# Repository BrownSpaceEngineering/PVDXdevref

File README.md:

# PVDX device reference

Datasheets for the PVDX cubesat peripherals w/ RAG

## Add a datasheet

1. Copy the PDF into `original/<peripheral>/`.
2. Run `uv run main.py ingest`.
3. Commit the new files in `original/` and `markdown/`.

The ingest step converts only new or changed files, so a second run is fast.

## GPU Acceleration

You can go super fast crazy mode by running on GPU if you have a CUDA-compatible NVIDIA gpu.
Run `uv run --extra gpu python -u main.py ingest`.

## Search

```
uv run main.py search "WHO_AM_I register" -k 5 --part 9-axis
```

## Layout

- `original/` source files provided by humans
- `markdown/` generated Markdown
- `index/` ingest-generated search index
- `boards/` KiCad board designs (schematics, PCB, gerbers), copied from the board repos

## Note on Datasheet Availability

All datasheets are made available in `original/` to the public except for those pertaining
to the CUBECOM STX-G2/VESTALINK, which are provided to BSE by CUBECOM. If you need these,
please request them from Alex Khosrowshahi (spoonmilk) or Alicia Wu.

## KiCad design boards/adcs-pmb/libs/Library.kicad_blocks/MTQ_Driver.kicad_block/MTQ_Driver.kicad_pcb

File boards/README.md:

# PVDX board designs

KiCad projects for the PVDX boards, copied from their BrownSpaceEngineering repos (not submodules).
The upstream repos are the source of truth for ongoing design work; re-copy to update.

KiCad lock files, `-backups/`, autosaves, `fp-info-cache`, `.kicad_prl`, and `.bak` files were left out.

| Folder | Upstream repo | Commit | Contents |
| --- | --- | --- | --- |
| `battery-board/` | [PVDX-Battery-Board](https://github.com/BrownSpaceEngineering/PVDX-Battery-Board) | `92fe52d` (2026-10-13) | Battery stack, heaters, thermistors; gerbers in `manufacturing/` |
| `compute-board/` | [PVDX-Compute-Board](https://github.com/BrownSpaceEngineering/PVDX-Compute-Board) | `c12a1c8` (2026-10-01) | SAMD51 compute board (2-layer `Compute Board/`, 4-layer `compute4layer/`), dev board, shared `Components/` |
| `solar-boards/` | [SolarBoards](https://github.com/BrownSpaceEngineering/SolarBoards) | `316883e` (2026-09-24) | Solar PCBs: `SolarPCB_Arm`, `SolarPCB_Long`, `SolarPCB_Short` with gerbers |
| `uhf-balun-board/` | [uhf-balun-board](https://github.com/BrownSpaceEngineering/uhf-balun-board) | `b9d6cff` (2026-09-22) | UHF balun board (newer revision, adds plated through-holes); gerbers in `gerbers/` |
| `balun-board/` | [balun-board](https://github.com/BrownSpaceEngineering/balun-board) | `164e4f9` (2026-09-16) | Earlier revision of the UHF balun board |
| `adcs-pmb/` | [PVDX-ADCS-PMB](https://github.com/BrownSpaceEngineering/PVDX-ADCS-PMB) | `089a12e` (2026-09-29) | ADCS + perovskite measurement board: photodiode amplifiers, magnetorquer drivers, perovskite pixel switching (`schematics/`); gerbers and plots in `manufacturing/` |
| `magnetorquer-board/` | [magnetorquer-board](https://github.com/BrownSpaceEngineering/magnetorquer-board) | `9018ce9` (2025-10-23) | Magnetorquer board |

Schematics are in `*.kicad_sch` files. These are plain-text S-expressions, so you can grep them for
symbol references, net labels, and part values.

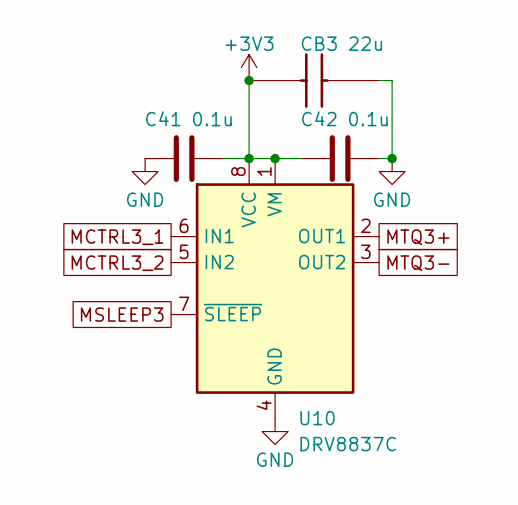
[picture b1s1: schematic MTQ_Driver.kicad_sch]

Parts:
C41, C42: 0.1u; C_0603_1608Metric
CB3: 22u; GRM18x; Mouser Part Number 81-GRM188R61A226ME5D
U10: DRV8837C; DSG8_P9X1P6_TEX

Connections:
+3V3: C41.2, C42.1, CB3.1, U10.1 (VM), U10.8 (VCC)
GND: C41.1, C42.2, CB3.2, U10.4 (GND), U10.9 (GND)
MCTRL3_1: U10.6 (IN1)
MCTRL3_2: U10.5 (IN2)
MSLEEP3: U10.7 (~SLEEP)
MTQ3+: U10.2 (OUT1)
MTQ3-: U10.3 (OUT2)

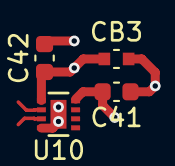
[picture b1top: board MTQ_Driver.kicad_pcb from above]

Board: 4 copper layers, 4 parts (0 on the bottom side), 2 nets.

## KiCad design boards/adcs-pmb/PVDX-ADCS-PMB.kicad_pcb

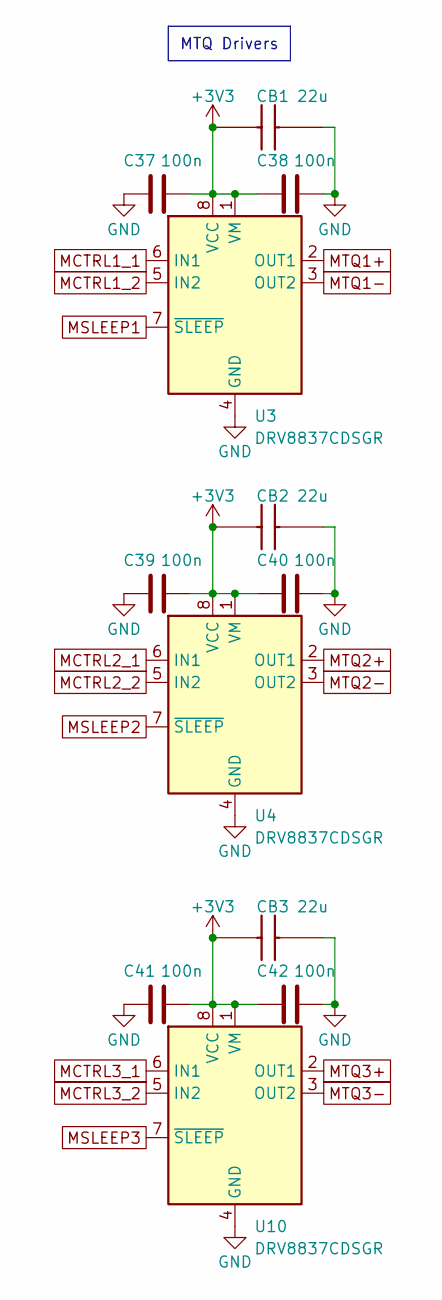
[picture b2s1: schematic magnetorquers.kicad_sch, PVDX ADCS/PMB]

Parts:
C37, C38, C39, C40, C41, C42: 100n; C_0603_1608Metric
CB1, CB2, CB3: 22u; GRM18x; Mouser Part Number 81-GRM188R61A226ME5D
U3, U4, U10: DRV8837CDSGR; DSG8_P9X1P6_TEX; Manufacturer_Part_Number DRV8837CDSGR

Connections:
+3V3: C37.2, C38.1, C39.2, C40.1, C41.2, C42.1, CB1.1, CB2.1, CB3.1, U3.1 (VM), U3.8 (VCC), U4.1 (VM), U4.8 (VCC), U10.1 (VM), U10.8 (VCC); also elsewhere on the board
GND: C37.1, C38.2, C39.1, C40.2, C41.1, C42.2, CB1.2, CB2.2, CB3.2, U3.4 (GND), U3.9 (GND), U4.4 (GND), U4.9 (GND), U10.4 (GND), U10.9 (GND); also elsewhere on the board
MCTRL1_1: U3.6 (IN1); also elsewhere on the board
MCTRL1_2: U3.5 (IN2); also elsewhere on the board
MCTRL2_1: U4.6 (IN1); also elsewhere on the board
MCTRL2_2: U4.5 (IN2); also elsewhere on the board
MCTRL3_1: U10.6 (IN1); also elsewhere on the board
MCTRL3_2: U10.5 (IN2); also elsewhere on the board
MSLEEP1: U3.7 (~SLEEP); also elsewhere on the board
MSLEEP2: U4.7 (~SLEEP); also elsewhere on the board
MSLEEP3: U10.7 (~SLEEP); also elsewhere on the board
MTQ1+: U3.2 (OUT1); also elsewhere on the board
MTQ1-: U3.3 (OUT2); also elsewhere on the board
MTQ2+: U4.2 (OUT1); also elsewhere on the board
MTQ2-: U4.3 (OUT2); also elsewhere on the board
MTQ3+: U10.2 (OUT1); also elsewhere on the board
MTQ3-: U10.3 (OUT2); also elsewhere on the board

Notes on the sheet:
MTQ Drivers

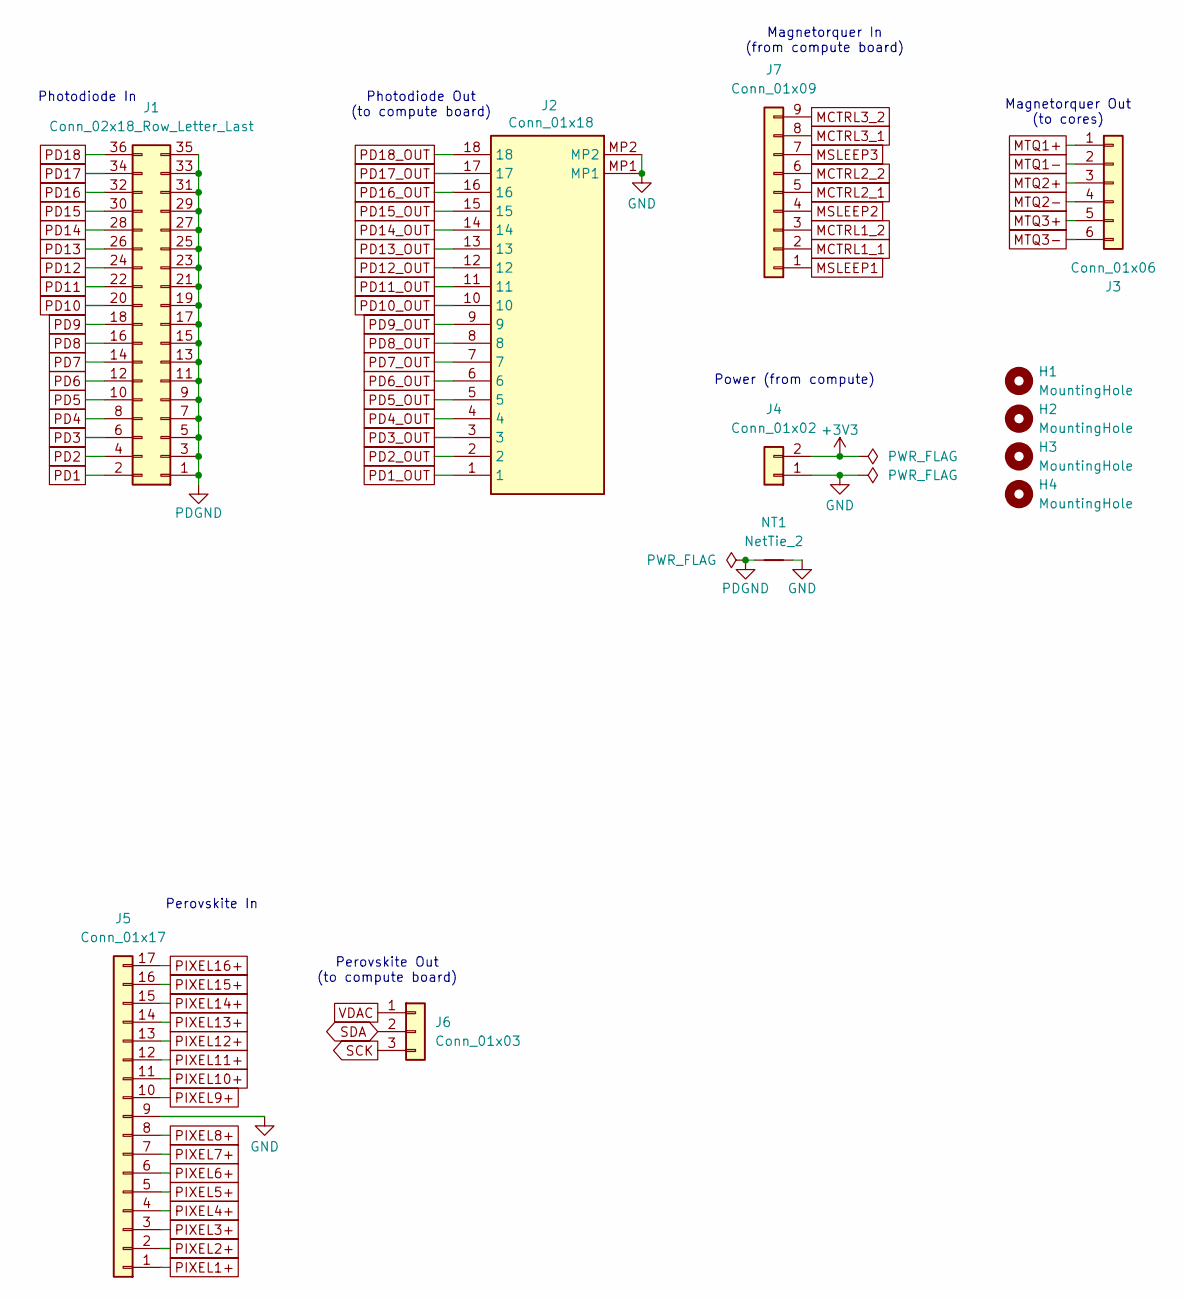
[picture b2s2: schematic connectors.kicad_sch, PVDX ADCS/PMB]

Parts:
H1, H2, H3, H4: MountingHole; MountingHole_3.4mm_M3_PVDX
J1: Conn_02x18_Row_Letter_Last; PinHeader_2x18_P2.54mm_Vertical
J2: Conn_01x18; FH34SRJ18S05SH50; Mouser Part Number 798-FH34SRJ18S05SH50
J3: Conn_01x06; PinHeader_1x06_P2.54mm_Vertical
J4: Conn_01x02; PinHeader_1x02_P2.54mm_Vertical
J5: Conn_01x17; PinHeader_1x17_P2.54mm_Vertical
J6: Conn_01x03; PinHeader_1x03_P2.54mm_Vertical
J7: Conn_01x09; PinHeader_1x09_P2.54mm_Vertical
NT1: NetTie_2; NetTie-2_SMD_Pad0.5mm

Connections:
+3V3: J4.2; also elsewhere on the board
GND: J2.MP1, J2.MP2, J4.1, J5.9, NT1.2; also elsewhere on the board
MCTRL1_1: J7.2; also elsewhere on the board
MCTRL1_2: J7.3; also elsewhere on the board
MCTRL2_1: J7.5; also elsewhere on the board
MCTRL2_2: J7.6; also elsewhere on the board
MCTRL3_1: J7.8; also elsewhere on the board
MCTRL3_2: J7.9; also elsewhere on the board
MSLEEP1: J7.1; also elsewhere on the board
MSLEEP2: J7.4; also elsewhere on the board
MSLEEP3: J7.7; also elsewhere on the board
MTQ1+: J3.1; also elsewhere on the board
MTQ1-: J3.2; also elsewhere on the board
MTQ2+: J3.3; also elsewhere on the board
MTQ2-: J3.4; also elsewhere on the board
MTQ3+: J3.5; also elsewhere on the board
MTQ3-: J3.6; also elsewhere on the board
PD1: J1.2; also elsewhere on the board
PD1_OUT: J2.1; also elsewhere on the board
PD2: J1.4; also elsewhere on the board
PD2_OUT: J2.2; also elsewhere on the board
PD3: J1.6; also elsewhere on the board
PD3_OUT: J2.3; also elsewhere on the board
PD4: J1.8; also elsewhere on the board
PD4_OUT: J2.4; also elsewhere on the board
PD5: J1.10; also elsewhere on the board
PD5_OUT: J2.5; also elsewhere on the board
PD6: J1.12; also elsewhere on the board
PD6_OUT: J2.6; also elsewhere on the board
PD7: J1.14; also elsewhere on the board
PD7_OUT: J2.7; also elsewhere on the board
PD8: J1.16; also elsewhere on the board
PD8_OUT: J2.8; also elsewhere on the board
PD9: J1.18; also elsewhere on the board
PD9_OUT: J2.9; also elsewhere on the board
PD10: J1.20; also elsewhere on the board
PD10_OUT: J2.10; also elsewhere on the board
PD11: J1.22; also elsewhere on the board
PD11_OUT: J2.11; also elsewhere on the board
PD12: J1.24; also elsewhere on the board
PD12_OUT: J2.12; also elsewhere on the board
PD13: J1.26; also elsewhere on the board
PD13_OUT: J2.13; also elsewhere on the board
PD14: J1.28; also elsewhere on the board
PD14_OUT: J2.14; also elsewhere on the board
PD15: J1.30; also elsewhere on the board
PD15_OUT: J2.15; also elsewhere on the board
PD16: J1.32; also elsewhere on the board
PD16_OUT: J2.16; also elsewhere on the board
PD17: J1.34; also elsewhere on the board
PD17_OUT: J2.17; also elsewhere on the board
PD18: J1.36; also elsewhere on the board
PD18_OUT: J2.18; also elsewhere on the board
PDGND: J1.1, J1.3, J1.5, J1.7, J1.9, J1.11, J1.13, J1.15, J1.17, J1.19, J1.21, J1.23, J1.25, J1.27, J1.29, J1.31, J1.33, J1.35, NT1.1; also elsewhere on the board
PIXEL1+: J5.1; also elsewhere on the board
PIXEL2+: J5.2; also elsewhere on the board
PIXEL3+: J5.3; also elsewhere on the board
PIXEL4+: J5.4; also elsewhere on the board
PIXEL5+: J5.5; also elsewhere on the board
PIXEL6+: J5.6; also elsewhere on the board
PIXEL7+: J5.7; also elsewhere on the board
PIXEL8+: J5.8; also elsewhere on the board
PIXEL9+: J5.10; also elsewhere on the board
PIXEL10+: J5.11; also elsewhere on the board
PIXEL11+: J5.12; also elsewhere on the board
PIXEL12+: J5.13; also elsewhere on the board
PIXEL13+: J5.14; also elsewhere on the board
PIXEL14+: J5.15; also elsewhere on the board
PIXEL15+: J5.16; also elsewhere on the board
PIXEL16+: J5.17; also elsewhere on the board
SCK: J6.3; also elsewhere on the board
SDA: J6.2; also elsewhere on the board
VDAC: J6.1; also elsewhere on the board

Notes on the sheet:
Magnetorquer Out (to cores)
Photodiode Out (to compute board)
Power (from compute)
Perovskite Out (to compute board)
Photodiode In
Magnetorquer In (from compute board)
Perovskite In

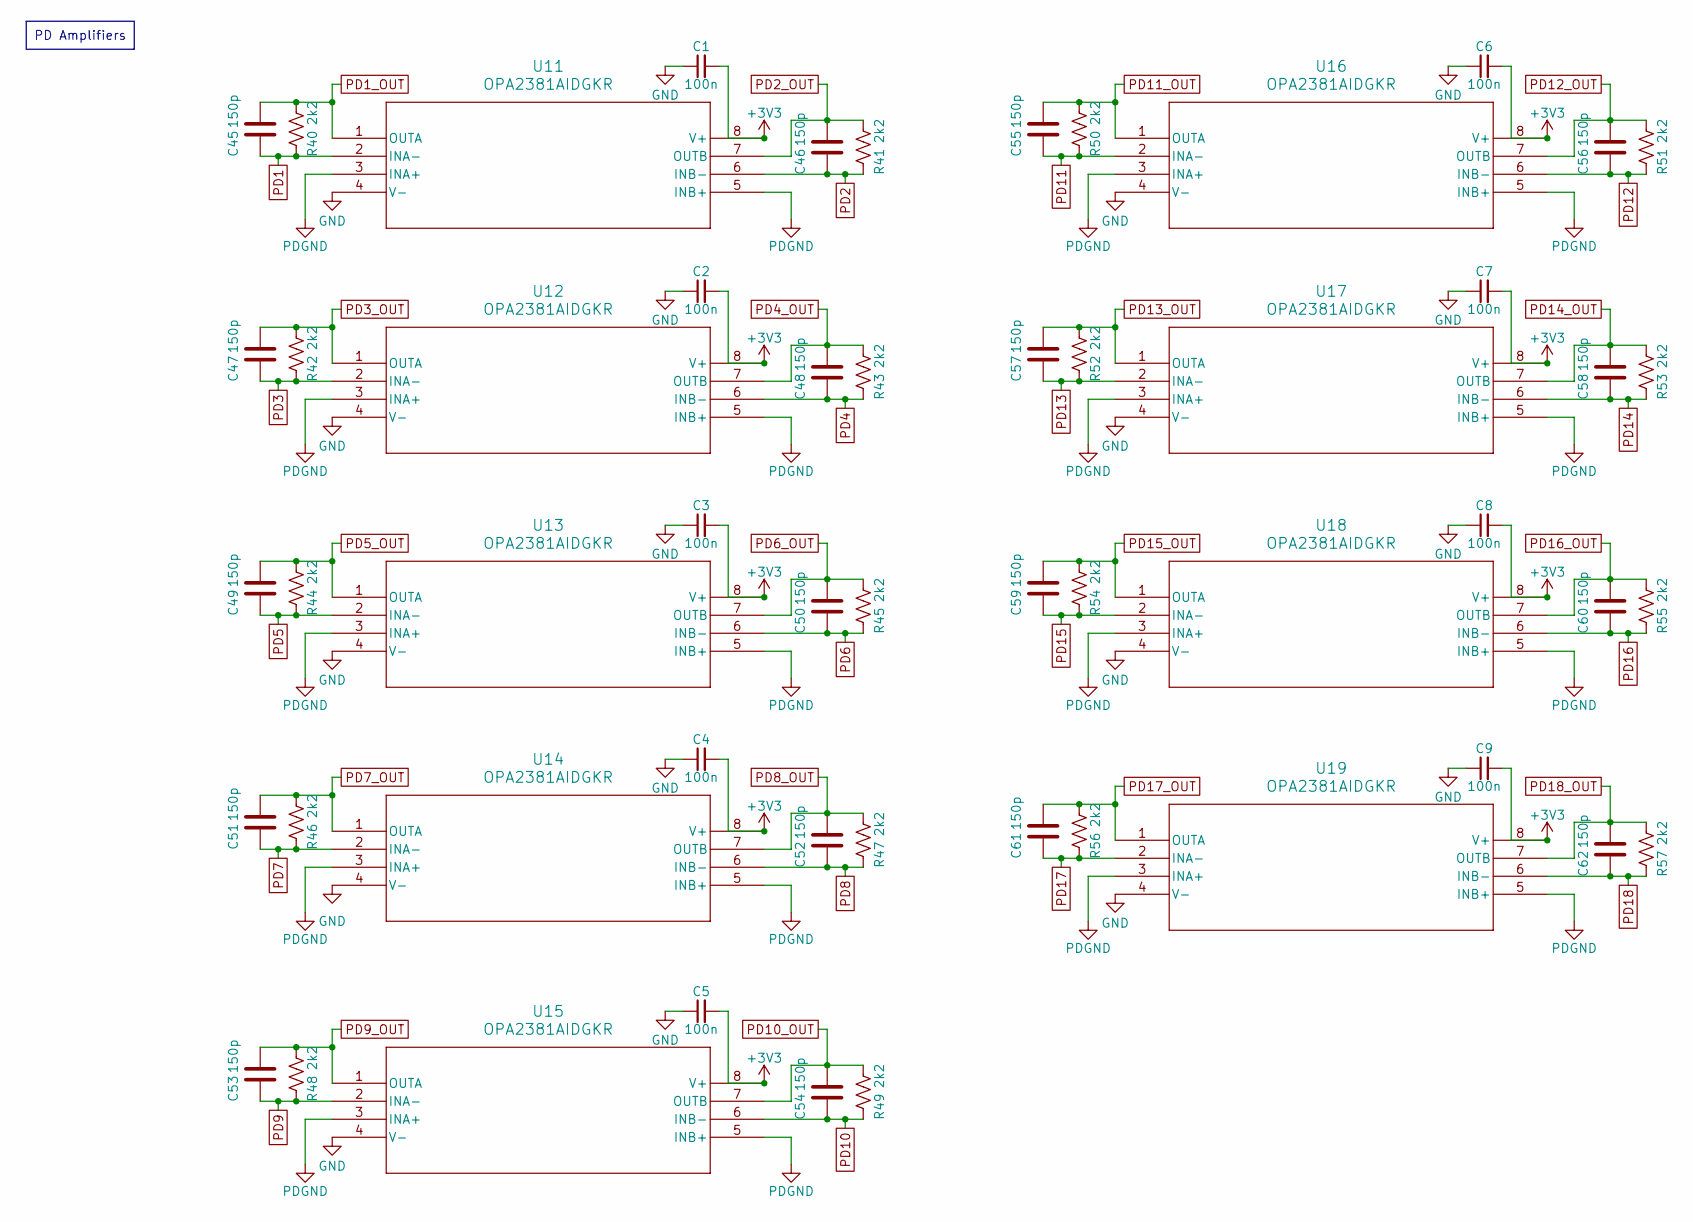
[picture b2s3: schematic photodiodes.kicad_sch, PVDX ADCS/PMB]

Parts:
C1, C2, C3, C4, C5, C6, C7, C8, C9: 100n; C_0402_1005Metric
C45, C46, C47, C48, C49, C50, C51, C52, C53, C54, C55, C56, C57, C58, C59, C60, C61, C62: 150p; C_0603_1608Metric
R40, R41, R42, R43, R44, R45, R46, R47, R48, R49, R50, R51, R52, R53, R54, R55, R56, R57: 2k2; R_0603_1608Metric
U11, U12, U13, U14, U15, U16, U17, U18, U19: OPA2381AIDGKR; DGK8; Manufacturer_Part_Number OPA2381AIDGKR

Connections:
+3V3: C1.2, C2.2, C3.2, C4.2, C5.2, C6.2, C7.2, C8.2, C9.2, U11.8 (V+), U12.8 (V+), U13.8 (V+), U14.8 (V+), U15.8 (V+), U16.8 (V+), U17.8 (V+), U18.8 (V+), U19.8 (V+); also elsewhere on the board
GND: C1.1, C2.1, C3.1, C4.1, C5.1, C6.1, C7.1, C8.1, C9.1, U11.4 (V-), U12.4 (V-), U13.4 (V-), U14.4 (V-), U15.4 (V-), U16.4 (V-), U17.4 (V-), U18.4 (V-), U19.4 (V-); also elsewhere on the board
PD1: C45.1, R40.1, U11.2 (INA-); also elsewhere on the board
PD1_OUT: C45.2, R40.2, U11.1 (OUTA); also elsewhere on the board
PD2: C46.1, R41.1, U11.6 (INB-); also elsewhere on the board
PD2_OUT: C46.2, R41.2, U11.7 (OUTB); also elsewhere on the board
PD3: C47.1, R42.1, U12.2 (INA-); also elsewhere on the board
PD3_OUT: C47.2, R42.2, U12.1 (OUTA); also elsewhere on the board
PD4: C48.1, R43.1, U12.6 (INB-); also elsewhere on the board
PD4_OUT: C48.2, R43.2, U12.7 (OUTB); also elsewhere on the board
PD5: C49.1, R44.1, U13.2 (INA-); also elsewhere on the board
PD5_OUT: C49.2, R44.2, U13.1 (OUTA); also elsewhere on the board
PD6: C50.1, R45.1, U13.6 (INB-); also elsewhere on the board
PD6_OUT: C50.2, R45.2, U13.7 (OUTB); also elsewhere on the board
PD7: C51.1, R46.1, U14.2 (INA-); also elsewhere on the board
PD7_OUT: C51.2, R46.2, U14.1 (OUTA); also elsewhere on the board
PD8: C52.1, R47.1, U14.6 (INB-); also elsewhere on the board
PD8_OUT: C52.2, R47.2, U14.7 (OUTB); also elsewhere on the board
PD9: C53.1, R48.1, U15.2 (INA-); also elsewhere on the board
PD9_OUT: C53.2, R48.2, U15.1 (OUTA); also elsewhere on the board
PD10: C54.1, R49.1, U15.6 (INB-); also elsewhere on the board
PD10_OUT: C54.2, R49.2, U15.7 (OUTB); also elsewhere on the board
PD11: C55.1, R50.1, U16.2 (INA-); also elsewhere on the board
PD11_OUT: C55.2, R50.2, U16.1 (OUTA); also elsewhere on the board
PD12: C56.1, R51.1, U16.6 (INB-); also elsewhere on the board
PD12_OUT: C56.2, R51.2, U16.7 (OUTB); also elsewhere on the board
PD13: C57.1, R52.1, U17.2 (INA-); also elsewhere on the board
PD13_OUT: C57.2, R52.2, U17.1 (OUTA); also elsewhere on the board
PD14: C58.1, R53.1, U17.6 (INB-); also elsewhere on the board
PD14_OUT: C58.2, R53.2, U17.7 (OUTB); also elsewhere on the board
PD15: C59.1, R54.1, U18.2 (INA-); also elsewhere on the board
PD15_OUT: C59.2, R54.2, U18.1 (OUTA); also elsewhere on the board
PD16: C60.1, R55.1, U18.6 (INB-); also elsewhere on the board
PD16_OUT: C60.2, R55.2, U18.7 (OUTB); also elsewhere on the board
PD17: C61.1, R56.1, U19.2 (INA-); also elsewhere on the board
PD17_OUT: C61.2, R56.2, U19.1 (OUTA); also elsewhere on the board
PD18: C62.1, R57.1, U19.6 (INB-); also elsewhere on the board
PD18_OUT: C62.2, R57.2, U19.7 (OUTB); also elsewhere on the board
PDGND: U11.3 (INA+), U11.5 (INB+), U12.3 (INA+), U12.5 (INB+), U13.3 (INA+), U13.5 (INB+), U14.3 (INA+), U14.5 (INB+), U15.3 (INA+), U15.5 (INB+), U16.3 (INA+), U16.5 (INB+), U17.3 (INA+), U17.5 (INB+), U18.3 (INA+), U18.5 (INB+), U19.3 (INA+), U19.5 (INB+); also elsewhere on the board

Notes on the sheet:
PD Amplifiers

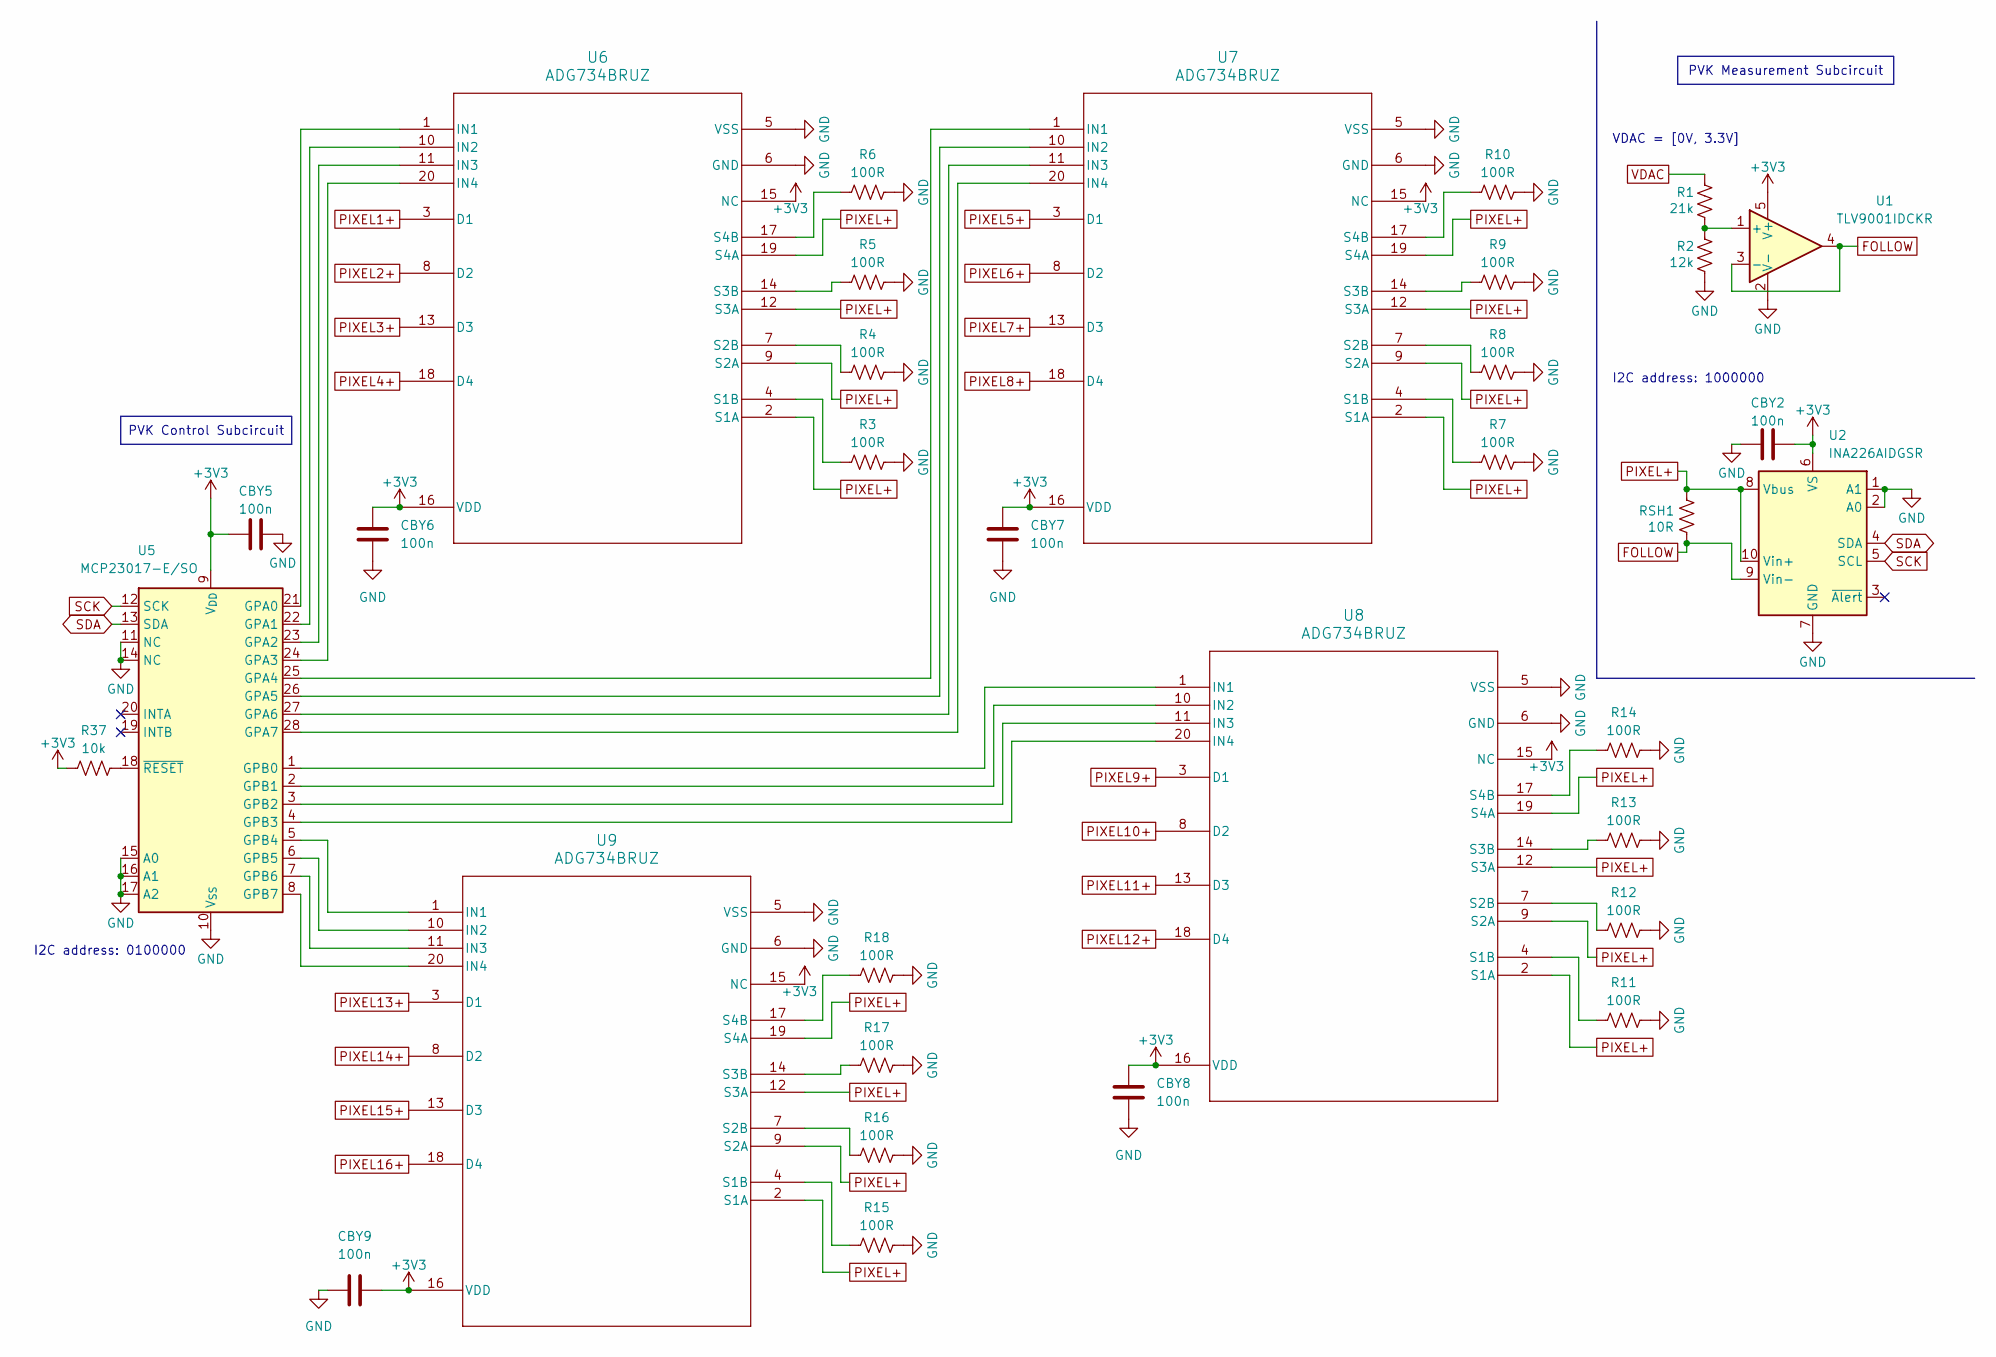
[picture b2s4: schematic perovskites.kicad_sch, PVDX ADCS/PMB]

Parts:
CBY2, CBY6, CBY7, CBY8, CBY9: 100n; C_0603_1608Metric
CBY5: 100n; C_0402_1005Metric
R1: 21k; R_0603_1608Metric; Manufacturer_Part_Number CRT0603-BY-2102ELF
R2: 12k; R_0603_1608Metric; Manufacturer_Part_Number CRT0603-BY-1202ELF
R3, R4, R5, R6, R7, R8, R9, R10, R11, R12, R13, R14, R15, R16, R17, R18: 100R; R_0603_1608Metric; Manufacturer_Part_Number ERJ-3EKF1000V
R37: 10k; R_0603_1608Metric
RSH1: 10R; R_0603_1608Metric; Manufacturer_Part_Number CRT0603-BY-10R0ELF
U1: TLV9001IDCKR; SOT-353_SC-70-5; Manufacturer_Part_Number TLV9001IDCKR
U2: INA226AIDGSR; TSSOP-10_3x3mm_P0.5mm; Manufacturer_Part_Number INA226AIDGSR
U5: MCP23017-E/SO; SOIC-28W_7.5x17.9mm_P1.27mm; Manufacturer_Part_Number MCP23017-E/SO
U6, U7, U8, U9: ADG734BRUZ; RU_20_ADI; Manufacturer_Part_Number ADG734BRUZ

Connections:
+3V3: CBY2.2, CBY5.1, CBY6.1, CBY7.1, CBY8.1, CBY9.2, R37.1, U1.5 (V+), U2.6 (VS), U5.9 (V_{DD}), U6.15 (NC), U6.16 (VDD), U7.15 (NC), U7.16 (VDD), U8.15 (NC), U8.16 (VDD), U9.15 (NC), U9.16 (VDD); also elsewhere on the board
FOLLOW: RSH1.1, U1.3 (-), U1.4, U2.9 (Vin-)
GND: CBY2.1, CBY5.2, CBY6.2, CBY7.2, CBY8.2, CBY9.1, R2.1, R3.2, R4.2, R5.2, R6.2, R7.2, R8.2, R9.2, R10.2, R11.2, R12.2, R13.2, R14.2, R15.2, R16.2, R17.2, R18.2, U1.2 (V-), U2.1 (A1), U2.2 (A0), U2.7 (GND), U5.10 (V_{SS}), U5.11 (NC), U5.14 (NC), U5.15 (A0), U5.16 (A1), U5.17 (A2), U6.5 (VSS), U6.6 (GND), U7.5 (VSS), U7.6 (GND), U8.5 (VSS), U8.6 (GND), U9.5 (VSS), U9.6 (GND); also elsewhere on the board
unnamed: R1.1, R2.2, U1.1 (+)
unnamed: U5.21 (GPA0), U6.1 (IN1)
unnamed: U5.22 (GPA1), U6.10 (IN2)
unnamed: U5.23 (GPA2), U6.11 (IN3)
unnamed: U5.24 (GPA3), U6.20 (IN4)
unnamed: U5.25 (GPA4), U7.1 (IN1)
unnamed: U5.26 (GPA5), U7.10 (IN2)
unnamed: U5.27 (GPA6), U7.11 (IN3)
unnamed: U5.28 (GPA7), U7.20 (IN4)
unnamed: U5.1 (GPB0), U8.1 (IN1)
unnamed: U5.2 (GPB1), U8.10 (IN2)
unnamed: U5.3 (GPB2), U8.11 (IN3)
unnamed: U5.4 (GPB3), U8.20 (IN4)
unnamed: U5.5 (GPB4), U9.1 (IN1)
unnamed: U5.6 (GPB5), U9.10 (IN2)
unnamed: U5.7 (GPB6), U9.11 (IN3)
unnamed: U5.8 (GPB7), U9.20 (IN4)
unnamed: R37.2, U5.18 (~RESET)
unnamed: R3.1, U6.4 (S1B)
unnamed: R4.1, U6.7 (S2B)
unnamed: R5.1, U6.14 (S3B)
unnamed: R6.1, U6.17 (S4B)
unnamed: R7.1, U7.4 (S1B)
unnamed: R8.1, U7.7 (S2B)
unnamed: R9.1, U7.14 (S3B)
unnamed: R10.1, U7.17 (S4B)
unnamed: R11.1, U8.4 (S1B)
unnamed: R12.1, U8.7 (S2B)
unnamed: R13.1, U8.14 (S3B)
unnamed: R14.1, U8.17 (S4B)
unnamed: R15.1, U9.4 (S1B)
unnamed: R16.1, U9.7 (S2B)
unnamed: R17.1, U9.14 (S3B)
unnamed: R18.1, U9.17 (S4B)
PIXEL1+: U6.3 (D1); also elsewhere on the board
PIXEL2+: U6.8 (D2); also elsewhere on the board
PIXEL3+: U6.13 (D3); also elsewhere on the board
PIXEL4+: U6.18 (D4); also elsewhere on the board
PIXEL5+: U7.3 (D1); also elsewhere on the board
PIXEL6+: U7.8 (D2); also elsewhere on the board
PIXEL7+: U7.13 (D3); also elsewhere on the board
PIXEL8+: U7.18 (D4); also elsewhere on the board
PIXEL9+: U8.3 (D1); also elsewhere on the board
PIXEL10+: U8.8 (D2); also elsewhere on the board
PIXEL11+: U8.13 (D3); also elsewhere on the board
PIXEL12+: U8.18 (D4); also elsewhere on the board
PIXEL13+: U9.3 (D1); also elsewhere on the board
PIXEL14+: U9.8 (D2); also elsewhere on the board
PIXEL15+: U9.13 (D3); also elsewhere on the board
PIXEL16+: U9.18 (D4); also elsewhere on the board
PIXEL+: RSH1.2, U2.8 (Vbus), U2.10 (Vin+), U6.2 (S1A), U6.9 (S2A), U6.12 (S3A), U6.19 (S4A), U7.2 (S1A), U7.9 (S2A), U7.12 (S3A), U7.19 (S4A), U8.2 (S1A), U8.9 (S2A), U8.12 (S3A), U8.19 (S4A), U9.2 (S1A), U9.9 (S2A), U9.12 (S3A), U9.19 (S4A)
SCK: U2.5 (SCL), U5.12 (SCK); also elsewhere on the board
SDA: U2.4 (SDA), U5.13 (SDA); also elsewhere on the board
VDAC: R1.2; also elsewhere on the board

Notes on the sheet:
I2C address: 0100000
VDAC = [0V, 3.3V]
I2C address: 1000000
PVK Measurement Subcircuit
PVK Control Subcircuit

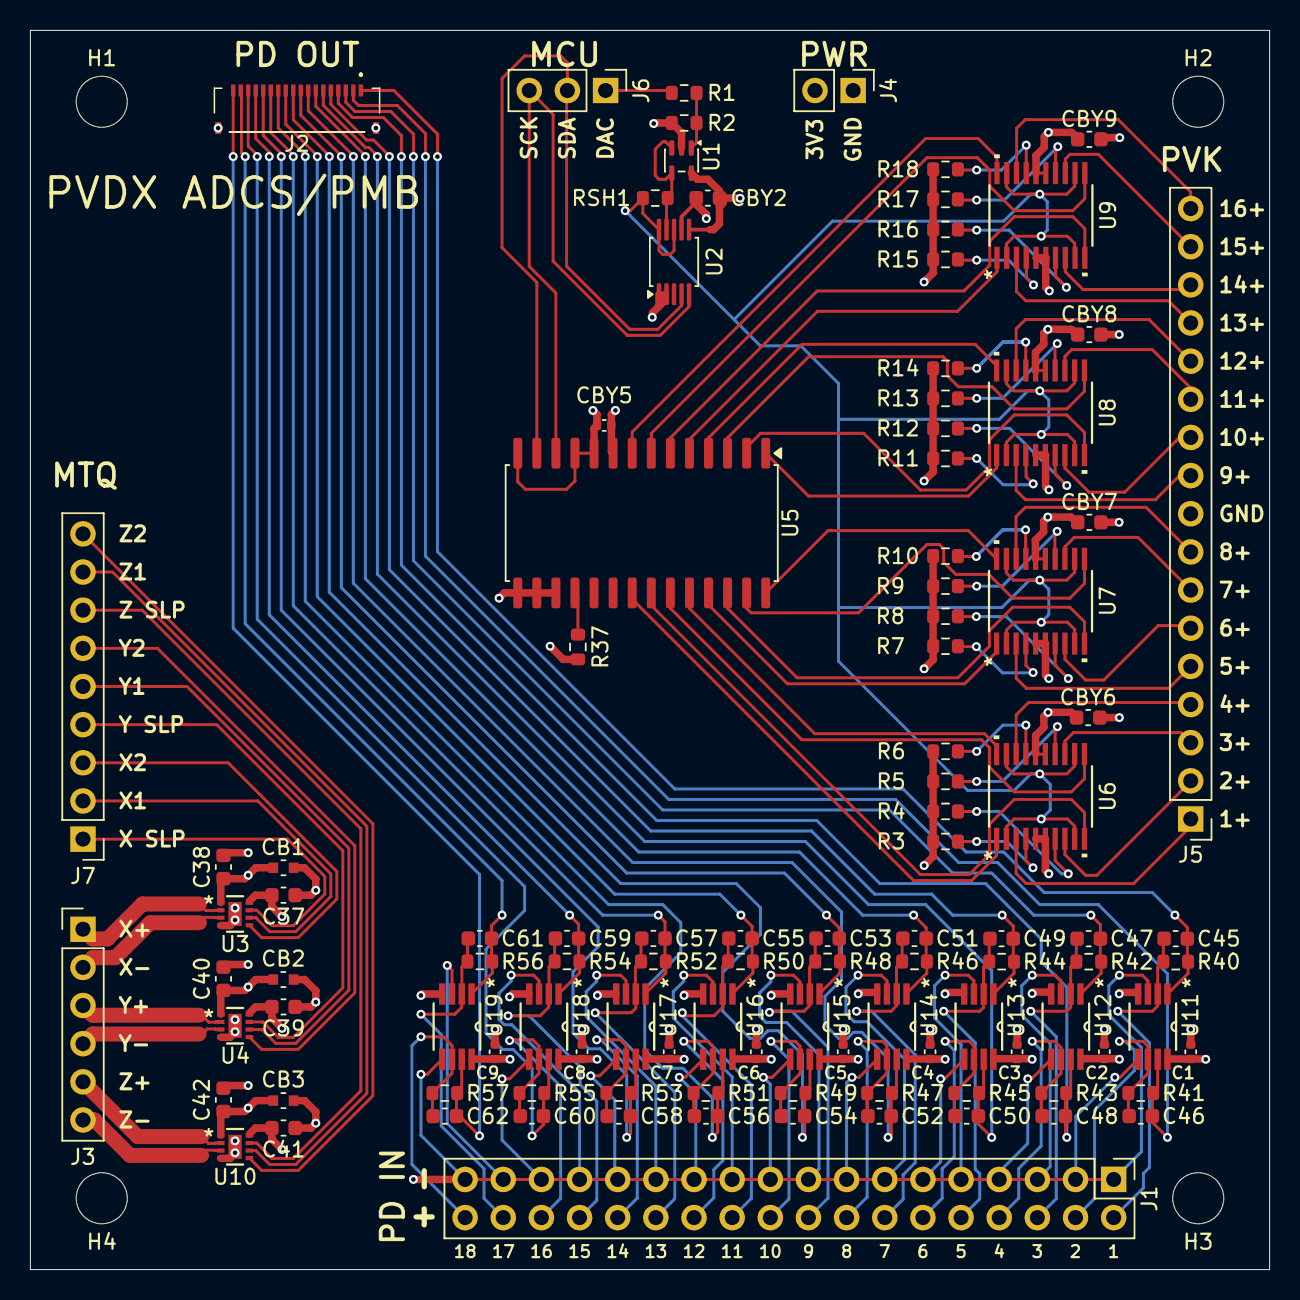
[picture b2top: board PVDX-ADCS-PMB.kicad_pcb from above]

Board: 4 copper layers, 82.5 x 82.5 mm, 111 parts (0 on the bottom side), 109 nets.

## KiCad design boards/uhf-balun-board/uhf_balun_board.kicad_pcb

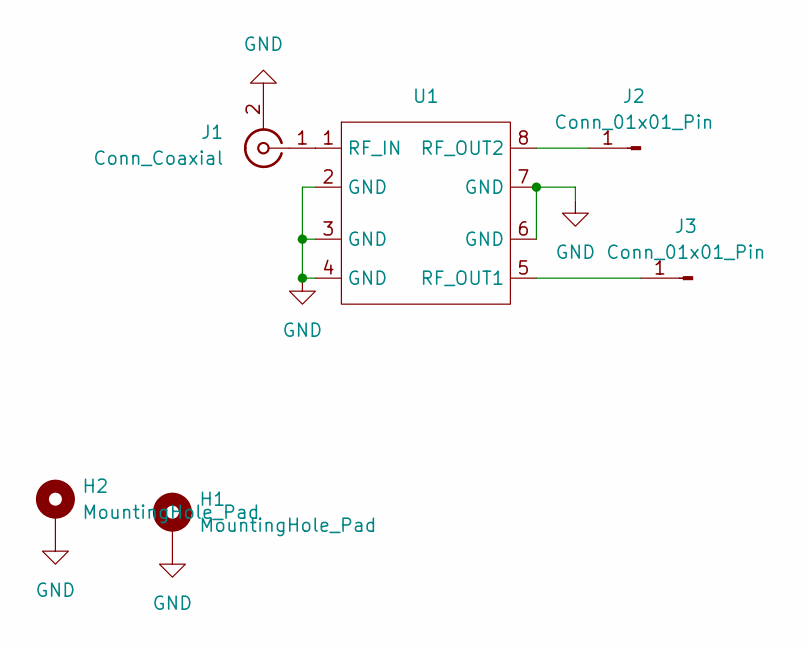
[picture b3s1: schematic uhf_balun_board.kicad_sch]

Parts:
H1, H2: MountingHole_Pad; MountingHole_2.7mm_Pad
J1: Conn_Coaxial; SMA_Samtec_SMA-J-P-H-ST-EM1_EdgeMount
J2, J3: Conn_01x01_Pin; TestPoint_Pad_2.0x2.0mm
U1: SYTX1-52HP-15W+_footprint

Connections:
GND: H1.1 (1_1), H2.1 (1_1), J1.2 (Ext), U1.2 (GND), U1.3 (GND), U1.4 (GND), U1.6 (GND), U1.7 (GND)
unnamed: J1.1 (In), U1.1 (RF_IN)
unnamed: J2.1 (Pin_1_1), U1.8 (RF_OUT2)
unnamed: J3.1 (Pin_1_1), U1.5 (RF_OUT1)

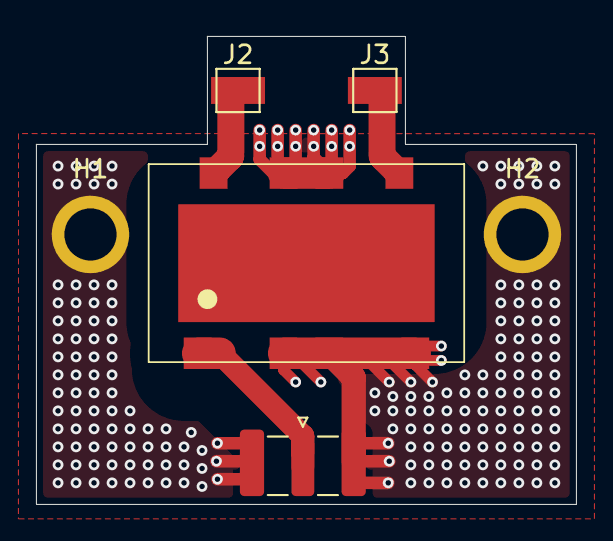
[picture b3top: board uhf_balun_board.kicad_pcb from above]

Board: 2 copper layers, 30.0 x 26.0 mm, 6 parts (0 on the bottom side), 4 nets.

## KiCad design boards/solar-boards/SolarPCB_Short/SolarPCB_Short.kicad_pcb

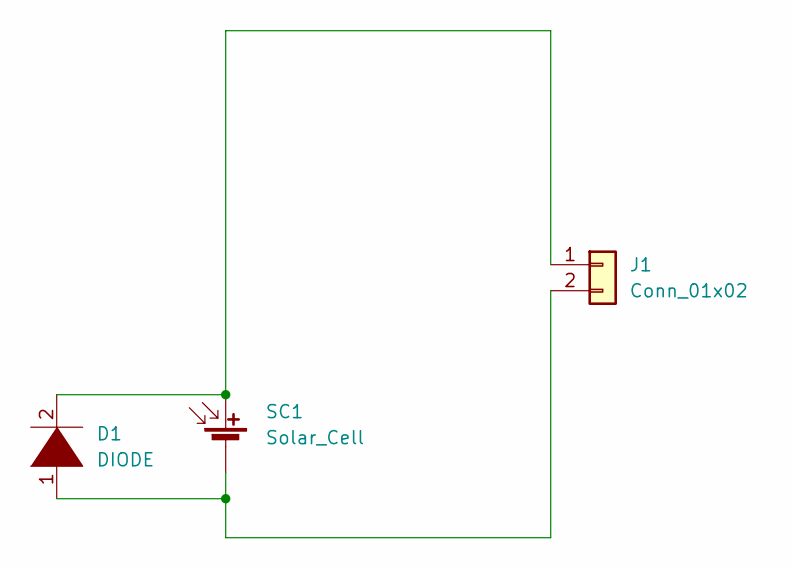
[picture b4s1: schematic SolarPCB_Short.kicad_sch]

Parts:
D1: DIODE; D_SMC_Handsoldering
J1: Conn_01x02; PinHeader_1x02_P2.54mm_Vertical
SC1: Solar_Cell; BSESolarCell2

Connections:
unnamed: D1.2 (A), J1.1, SC1.1 (+)
unnamed: D1.1 (K), J1.2, SC1.2 (-)

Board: 2 copper layers, 3 parts (0 on the bottom side), 2 nets, no tracks yet.

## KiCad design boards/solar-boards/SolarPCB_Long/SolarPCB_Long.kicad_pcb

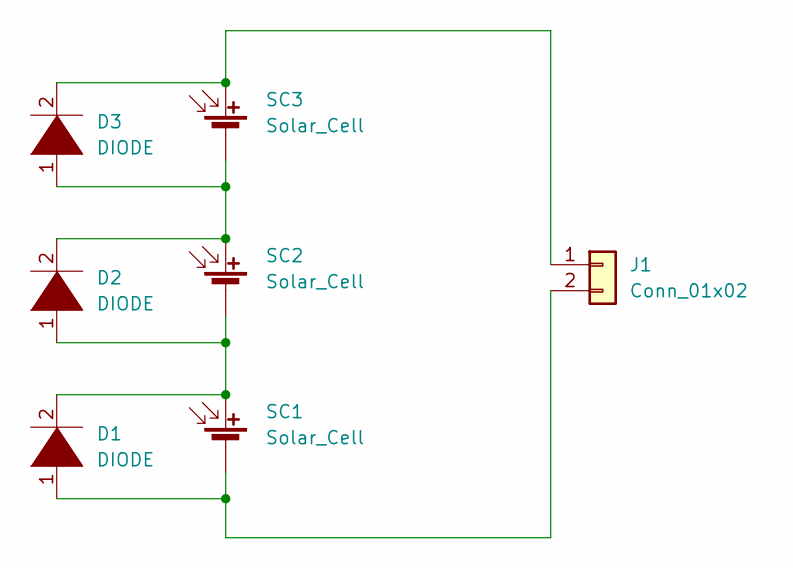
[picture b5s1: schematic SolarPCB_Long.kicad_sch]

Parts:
D1, D2, D3: DIODE; D_SMC_Handsoldering
J1: Conn_01x02; PinHeader_1x02_P2.54mm_Vertical
SC1, SC2, SC3: Solar_Cell; BSESolarCell2

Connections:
unnamed: D1.2 (A), D2.1 (K), SC1.1 (+), SC2.2 (-)
unnamed: D1.1 (K), J1.2, SC1.2 (-)
unnamed: D3.2 (A), J1.1, SC3.1 (+)
unnamed: D2.2 (A), D3.1 (K), SC2.1 (+), SC3.2 (-)

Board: 2 copper layers, 7 parts (0 on the bottom side), 4 nets, no tracks yet.
